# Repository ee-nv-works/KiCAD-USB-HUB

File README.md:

# KiCAD-USB-HUB
6 port usb hub based off USB2507

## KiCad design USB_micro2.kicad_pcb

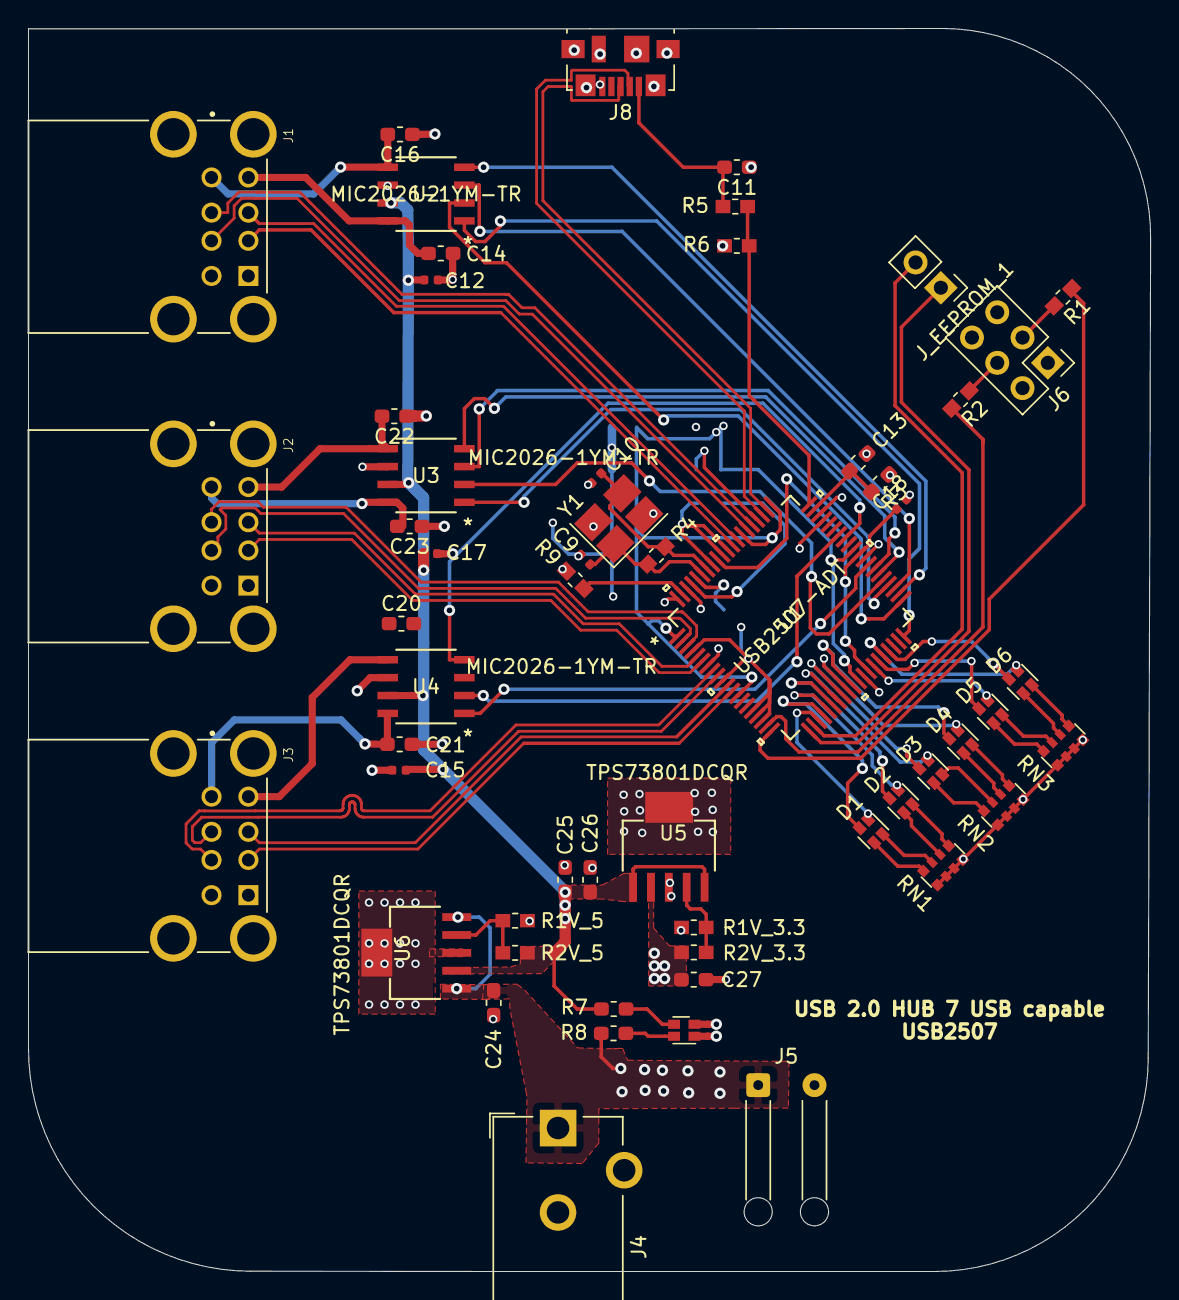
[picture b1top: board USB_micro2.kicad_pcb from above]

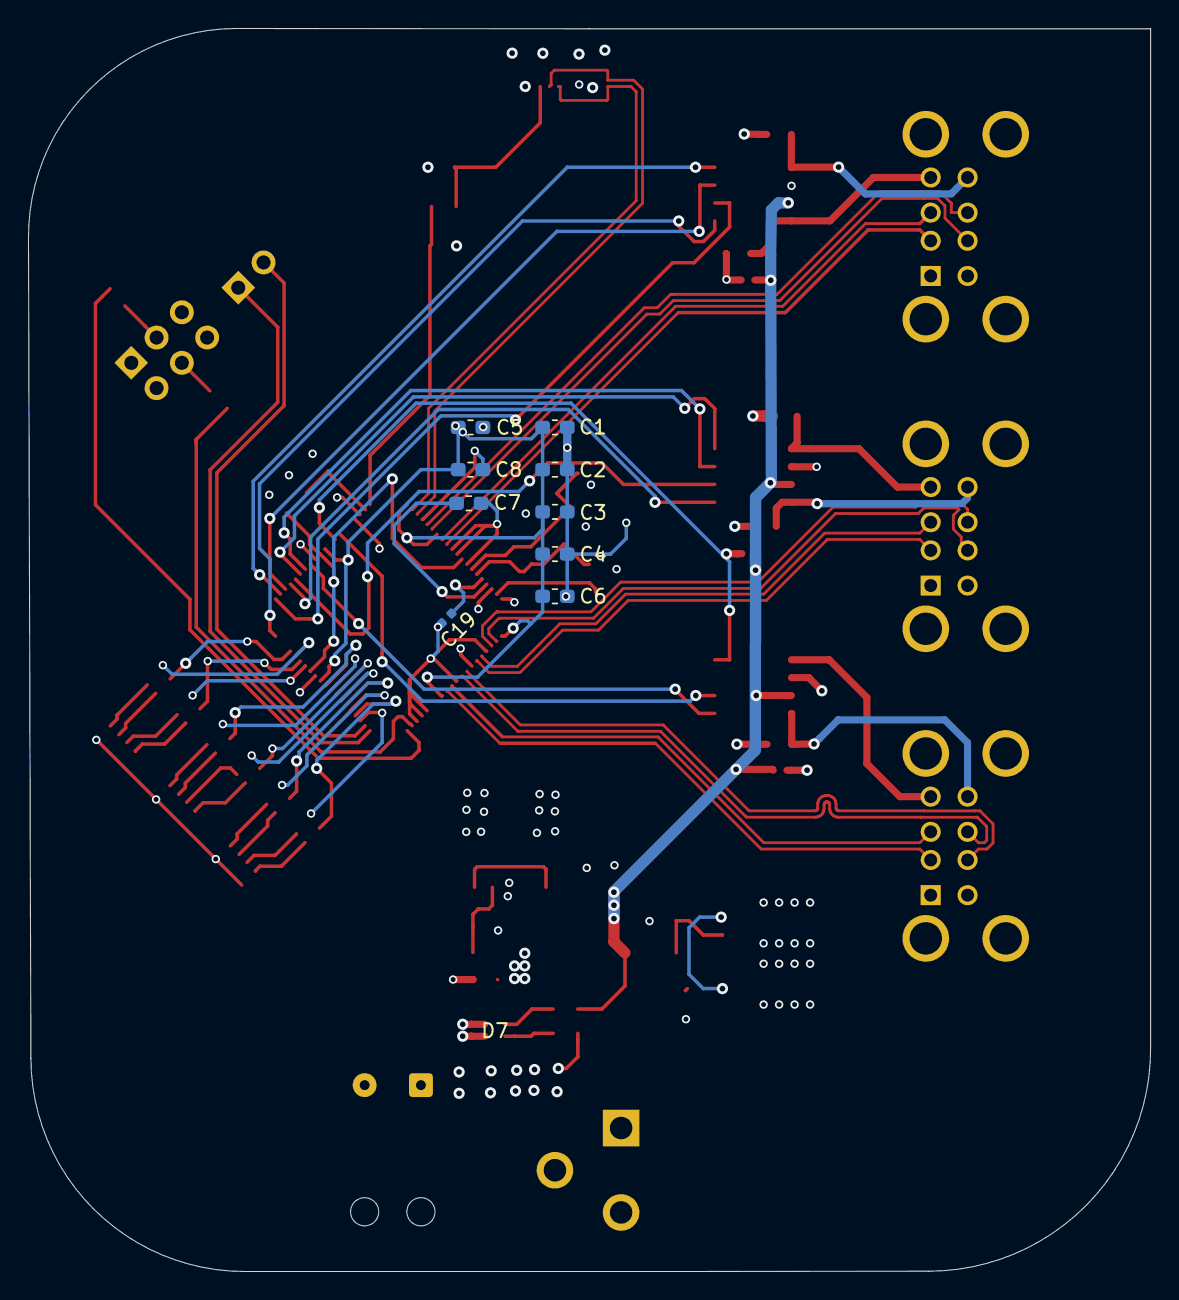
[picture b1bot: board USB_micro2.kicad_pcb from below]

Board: 4 copper layers, 79.7 x 88.3 mm, 65 parts (9 on the bottom side), 77 nets.

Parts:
C1, C2, C4, C5, C6, C7, C11, C13: 0.1u; C_0603_1608Metric_Pad1.05x0.95mm_HandSolder
C3, C8, C24, C25, C26, C27: 10u; C_0603_1608Metric_Pad1.05x0.95mm_HandSolder
C9, C10: 33p; C_0402_1005Metric
C12, C15, C17: 0.1u; C_0402_1005Metric
C14, C16, C20, C21, C22, C23: 47u; C_0603_1608Metric_Pad1.05x0.95mm_HandSolder
C18, C19: 4.7u; C_0402_1005Metric
D1, D2, D3, D4, D5, D6, D7: LED_Dual_ACAC; Dual_LED
J1, J2, J3: UJ2-USB_A-1-TH; CUI_UJ2-USB_A-1-TH
J4: Barrel_Jack_Switch; BarrelJack_CUI_PJ-102AH_Horizontal
J5: Screw_Terminal_01x02; solderWires_2xrelief_20AWG
J6: Conn_2Rows-05Pins_MountingPin; PinHeader_2x03_P2.54mm_Vertical
J8: USB_B_Micro; USB_Micro-B_Molex_47346-0001
J_EEPROM_1: Conn_2Rows-05Pins_MountingPin; PinHeader_1x02_P2.54mm_Vertical
R1, R2: 10k; R_0603_1608Metric_Pad1.05x0.95mm_HandSolder
R1V_3.3: 5.9K1%; R_0603_1608Metric_Pad1.05x0.95mm_HandSolder
R1V_5: 3.6K1%; R_0603_1608Metric_Pad1.05x0.95mm_HandSolder
R2V_3.3: 10K1%; R_0603_1608Metric_Pad1.05x0.95mm_HandSolder
R2V_5: 12K1%; R_0603_1608Metric_Pad1.05x0.95mm_HandSolder
R3, R5, R6: 100K; R_0603_1608Metric_Pad1.05x0.95mm_HandSolder
R4: 1Meg; R_0603_1608Metric_Pad1.05x0.95mm_HandSolder
R7: 330; R_0603_1608Metric_Pad1.05x0.95mm_HandSolder
R8: 1k; R_0603_1608Metric_Pad1.05x0.95mm_HandSolder
R9: 12K; R_0603_1608Metric_Pad1.05x0.95mm_HandSolder
RN1, RN2, RN3: R_Network04; R_singleConvex_4x0612
U1: USB2507-ADT
U2, U3, U4: MIC2026-1YM-TR
U5, U6: TPS73801DCQR
Y1: 24Mhz; Crystal_SMD_SeikoEpson_FA238-4Pin_3.2x2.5mm_HandSoldering

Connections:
3.3V: C1.1, C2.1, C3.1, C4.1, C5.1, C6.1, C7.1, C8.1, C27.1, J6.1, J6.2, R2V_3.3.2, R3.1, RN1.1, RN2.1, RN3.1, U1.1, U1.7, U1.13, U1.31, U1.51, U1.58, U1.61, U1.67, U1.77, U1.78, U5.2
5.0V: C12.1, C15.1, C17.1, C25.1, C26.2, R2V_5.2, R7.2, U2.7, U3.7, U4.7, U5.1, U5.5, U6.2
12V: C24.2, J4.1, J5.1, R8.2, U6.1, U6.5
AM1: D1.4, U1.23
AM2: D2.4, U1.25
AM3: D3.4, U1.27
AM4: D4.4, U1.29
AM5: D5.4, U1.34
AM6: D6.4, U1.36
CFG_SEL1: R1.1, U1.20
CLK1: C9.1, R4.1, U1.75, Y1.1
CLK2: C10.1, R4.2, U1.74, Y1.3
D1+: J1.3, U1.66
D1-: J1.2, U1.65
D2+: J1.7, U1.69
D2-: J1.6, U1.68
D3+: J2.3, U1.2
D3-: J2.2, U1.3
D4+: J2.7, U1.6
D4-: J2.6, U1.5
D5+: J3.3, U1.8
D5-: J3.2, U1.9
D6+: J3.7, U1.12
D6-: J3.6, U1.11
GR1: D1.2, U1.24
GR2: D2.2, U1.26
GR3: D3.2, U1.28
GR4: D4.2, U1.30
GR5: D5.2, U1.35
GR6: D6.2, U1.37
MGND: C1.2, C2.2, C3.2, C4.2, C5.2, C6.2, C7.2, C8.2, C9.2, C10.2, C11.1, C12.2, C13.2, C14.1, C15.2, C16.1, C17.2, C18.2, C19.2, C20.1, C21.1, C22.1, C23.1, C24.1, C25.2, C26.1, C27.2, D7.2, D7.4, J1.4, J1.8, J1.SH1, J1.SH2, J1.SH3, J1.SH4, J2.4, J2.8, J2.SH1, J2.SH2, J2.SH3, J2.SH4, J3.4, J3.8, J3.SH1, J3.SH2, J3.SH3, J3.SH4, J4.2, J4.3, J5.2, J6.5, J6.6, J8.5, J8.6, R1V_3.3.2, R1V_5.2, R6.1, R9.2, U1.4, U1.10, U1.16, U1.17, U1.18, U1.32, U1.49, U1.57, U1.64, U1.70, U1.71, U1.73, U1.80, U2.6, U3.6, U4.6, U5.3, U6.3, Y1.2, Y1.4
unnamed: C11.2, J8.1, R5.1
unnamed: C13.1, R3.2, U1.59
unnamed: D1.1, RN1.5
unnamed: D1.3, RN1.4
unnamed: D2.1, RN1.3
unnamed: D2.3, RN1.2
unnamed: D3.1, RN2.5
unnamed: D3.3, RN2.4
unnamed: D4.1, RN2.3
unnamed: D4.3, RN2.2
unnamed: D5.1, RN3.5
unnamed: D5.3, RN3.4
unnamed: D6.1, RN3.3
unnamed: D6.3, RN3.2
unnamed: D7.1, R7.1
unnamed: D7.3, R8.1
unnamed: J6.3, R1.2
unnamed: J6.4, R2.1
unnamed: R1V_3.3.1, R2V_3.3.1, U5.4
unnamed: R1V_5.1, R2V_5.1, U6.4
unnamed: R9.1, U1.79
OCS_1: U1.41, U2.2
OCS_2: U1.43, U2.3
OCS_3: U1.45, U3.2
OCS_4: U1.47, U3.3
OCS_6: U1.54, U4.2
SCL: J_EEPROM_1.1, U1.21
SDA: J_EEPROM_1.2, U1.22
SELF_PWR: R2.2, U1.19
USBpwr1a: U1.40, U2.1
USBpwr1b: U1.42, U2.4
USBpwr2a: U1.44, U3.1
USBpwr2b: U1.46, U3.4
USBpwr3a: U1.48, U4.1
USBpwr3b: U1.53, U4.4
VBUS_MAIN: R5.2, R6.2, U1.60
VDC18: C18.1, U1.33, U1.50, U1.72
VDC19: C19.1, U1.76
Vbus1a: C16.2, J1.1, U2.5
Vbus1b: C14.2, J1.5, U2.8
Vbus2a: C23.2, J2.1, U3.8
Vbus2b: C22.2, J2.5, U3.5
Vbus3a: C21.2, J3.1, U4.8
Vbus3b: C20.2, J3.5, U4.5
_UPD+: J8.3, U1.62
_UPD-: J8.2, U1.63

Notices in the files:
parts and their libraries:
Copyright 2016 Accelerated Designs. All rights reserved.
